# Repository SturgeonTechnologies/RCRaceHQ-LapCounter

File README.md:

# RCRaceHQ-LapCounter

Offline-first RC lap counter that runs on a Raspberry Pi 4 at the track and
syncs to [RC Race HQ](https://www.rcracehq.com). Decoding is done by
[OpenStint](https://github.com/zsellera/openstint) with an RTL-SDR; this repo
holds the services and web UI around it, and the hardware.

| Path | What |
|---|---|
| [`app/`](app) | The app: `lapd` (decoder feed → SQLite) + `web` (setup, admin, live view). Python, one container image |
| [`docs/design.md`](docs/design.md) | Architecture and build order |
| [`docs/club-sync.md`](docs/club-sync.md) | Club sync with RC Race HQ: pairing, event download, check-in, scoring, takeover |
| [`docs/linking.md`](docs/linking.md) | Linking a Pi to a club's track in RC Race HQ (Settings → Link) |
| [`docs/racing.md`](docs/racing.md) | Running a heat: start, countdown, laps, finish, results, qualifying |
| [`docs/event-sync.md`](docs/event-sync.md) | Downloading the club's events (Events page), the event pack format, transponders to learn |
| [`docs/build.md`](docs/build.md) | Building the image, CI → GHCR (native arm64), releases |
| [`hardware/burst-detector-hat/`](hardware/burst-detector-hat) | Burst-detector HAT for the Pi (KiCad, fab files) |
| [`hardware/lapcounter-hat/`](hardware/lapcounter-hat) | Rev 1.1 all-in-one HAT: baluns, track/pad relay, amp, detector, ID EEPROM |

## Where things live

- **This repo**: the code that runs as the service, and its image.
  CI tests every PR, builds `linux/arm64` on an arm64 runner, and on `main` /
  `v*` tags pushes to `ghcr.io/sturgeontechnologies/rcracehq-lapcounter`.
- **[RCRaceHQ-LapCounter-Deploy](https://github.com/SturgeonTechnologies/RCRaceHQ-LapCounter-Deploy)**:
  the Ansible. Provisions the Pi (OpenStint decoder, event hotspot + captive
  portal, SSM registration) and deploys a pinned image tag of this app with
  `deploy_lapcounter_app.yml`. It used to be `deploy/ansible/` here.

## Quick start

```bash
cd app
pip install -e '.[test]' && pytest       # tests
docker compose up --build                # web on :8080, lapd → 127.0.0.1:5556
```

Ship a version: merge to `main` (pushes `:sha-<7>`) or tag `vX.Y.Z` (pushes
`:vX.Y.Z`), then set `lapcounter_app_image_tag` in the deploy repo's inventory
and run its `deploy_lapcounter_app.yml`. Details in [docs/build.md](docs/build.md).

## License

Source-available. Software is [FSL-1.1-ALv2](LICENSE) (becomes Apache-2.0 two
years after each release); the HAT board in `hardware/` is
[CERN-OHL-S-2.0](hardware/LICENSE). Plain-language summary in
[LICENSING.md](LICENSING.md). "RC Race HQ" is a trademark of Sturgeon
Technologies LLC.

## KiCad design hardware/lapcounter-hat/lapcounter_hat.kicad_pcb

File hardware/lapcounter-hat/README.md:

# Lap counter HAT, rev 1.1 (all-in-one RF front end)

Raspberry Pi 4 HAT (65 × 56.5 mm, M2.5 HAT holes). Everything between the
loops and the RTL-SDR v3 is on this board: loop inputs, 1:9 baluns, the
track/pad relay, a 3–8 MHz band-pass, the LMH6624 amp with a bypass relay,
the burst detector and the HAT ID EEPROM.

```
track loop -> TB1 screw terminal -> T1 1:9 balun -+- or J1 SMA (balun + coax at the loop)
pad loop   -> TB2 screw terminal -> T2 1:9 balun -+- or J5 SMA
   -> K1 (GPIO22: off = TRACK, on = PAD; the other input is grounded)
   -> TVS -> 3–8 MHz band-pass -> K2 (GPIO27: off = AMP +21 dB, on = BYPASS)
   -> splitter -+-> J2 SMA -> RTL-SDR v3 (IDs via OpenStint)
                +-> AD8307 RSSI -> ADS1115 (I2C 0x48) + LM393 -> GPIO17 + BURST LED
U5 24C32 on ID_SD/ID_SC (pins 27/28), write-protected unless JP1 is bridged.
```

Use **either** the screw terminal **or** the SMA jack on each input, not both.
- Screw terminal: loop wire or twisted pair runs straight to the board; the on-board balun does the job.
- SMA jack: the club already has a balun at the loop and coax to the table.
Put a 390 Ω resistor across the far end of each loop either way.

## Ordering (JLCPCB)
- Gerbers: `fab/lapcounter_hat_gerbers.zip` (2 layers, 1.6 mm, HASL).
- Assembly (top side): `fab/bom_jlcpcb.csv` + `fab/cpl_jlcpcb.csv`.
  Check every LCSC part is in stock and the pin-1 rotation of U1–U5 in JLC's preview.
- Fit by hand: J3 2×20 stacking header, T1/T2 (hand-wound 1:9 on FT37-43,
  8 trifilar turns), optional J4 PoE pass-through.

## Bring-up
1. Power from the Pi. `i2cdetect -y 1` shows `48`.
2. Drive GPIO22 high (`pinctrl set 22 op dh`) -> PAD LED on, relay clicks. `dl` -> back to TRACK.
3. Drive GPIO27 high -> BYPASS LED on (amp out of the path).
4. Turn RV1 until BURST goes out with the loop empty, then back off a little.
5. Transponder on the loop: BURST LED on, OpenStint decodes through J2.
6. Bridge JP1, write the HAT EEPROM (serial + UUID), then clear JP1.

## Rebuild
`source ~/tools/kicad-env.sh && JAVA=... FREEROUTING=... tools/build.sh`
regenerates everything from `tools/design.py` (single source of truth),
autoroutes with Freerouting, runs ERC/DRC (`fab/reports/`) and rewrites `fab/`.

Licensed CERN-OHL-S-2.0 (see repository `LICENSING.md`).

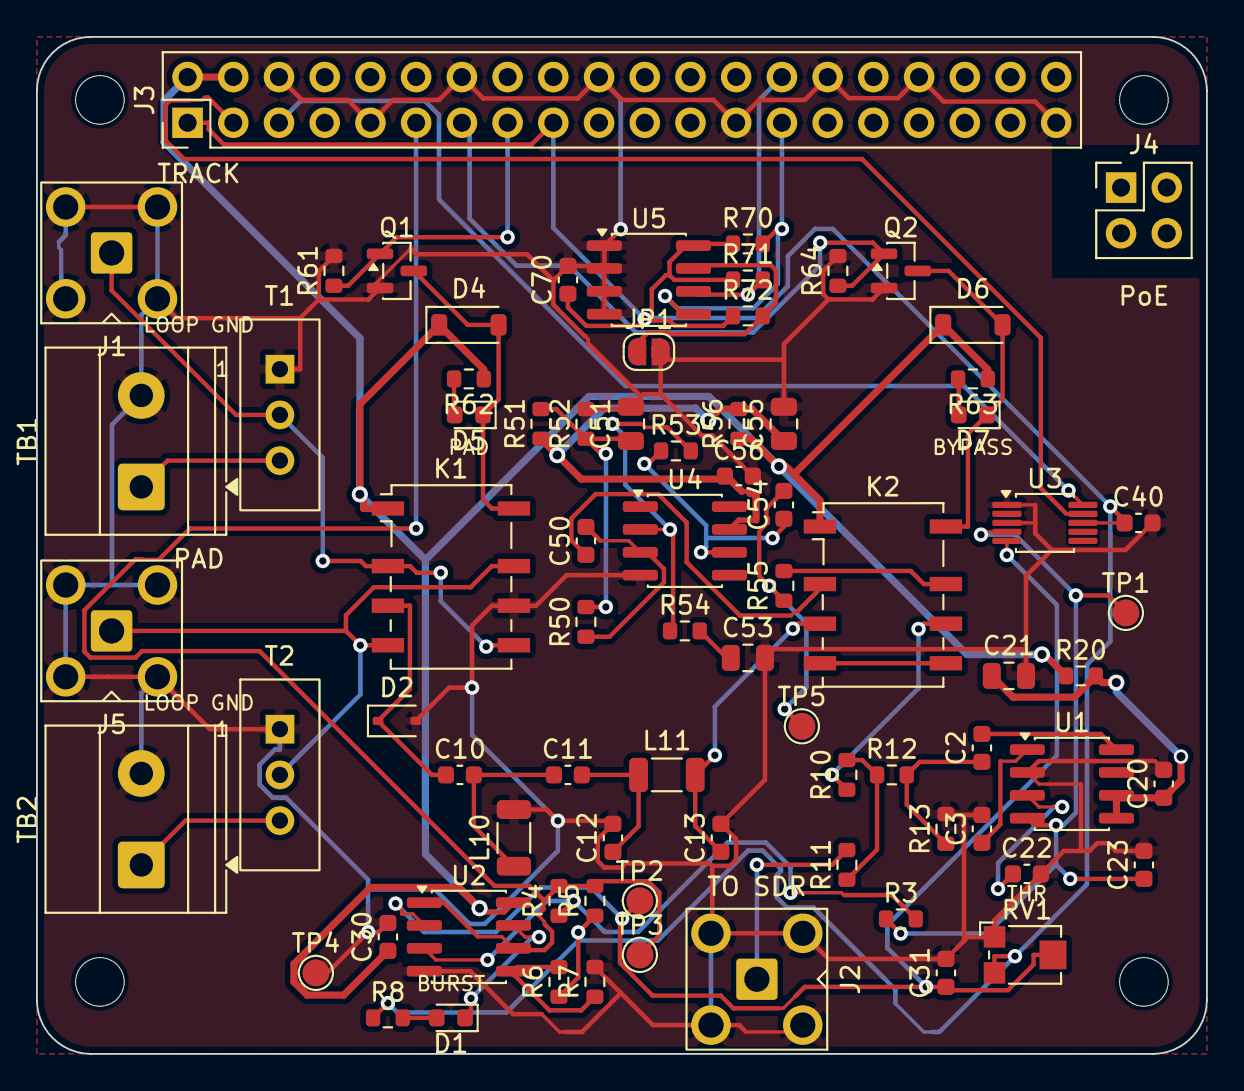
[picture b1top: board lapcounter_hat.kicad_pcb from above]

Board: 2 copper layers, 65.0 x 56.5 mm, 82 parts (0 on the bottom side), 47 nets.

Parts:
C2, C3: 10n; C_0603_1608Metric
C10, C11: 1n C0G; C_0603_1608Metric
C12, C13: 390p C0G; C_0603_1608Metric
C20, C30, C31, C40, C50, C54, C56, C70: 100n; C_0603_1608Metric
C21, C51, C53, C55: 10u; C_0805_2012Metric
C22: 1n; C_0603_1608Metric
C23: 470p C0G; C_0603_1608Metric
D1: BURST (green); LED_0603_1608Metric
D2: PESD5V0S1BA; D_SOD-323
D4, D6: 1N4148W; D_SOD-123
D5: PAD (green); LED_0603_1608Metric
D7: BYPASS (green); LED_0603_1608Metric
H1, H2, H3, H4: M2.5; MountingHole_2.7mm_M2.5
J1: TRACK (SMA); SMA_BAT_Wireless_BWSMA-KWE-Z001
J2: TO SDR; SMA_BAT_Wireless_BWSMA-KWE-Z001
J3: Pi GPIO (2x20 stacking); PinHeader_2x20_P2.54mm_Vertical
J4: PoE pass-through (not connected); PinHeader_2x02_P2.54mm_Vertical
J5: PAD (SMA); SMA_BAT_Wireless_BWSMA-KWE-Z001
JP1: WP (bridge to write); SolderJumper-2_P1.3mm_Open_RoundedPad1.0x1.5mm
K1: G6K-2F-Y 5V TRACK/PAD; Relay_DPDT_Omron_G6K-2F-Y
K2: G6K-2F-Y 5V AMP/BYPASS; Relay_DPDT_Omron_G6K-2F-Y
L10: 1.5u; L_1206_3216Metric
L11: 2.2u; L_1206_3216Metric
Q1, Q2: AO3400A; SOT-23
R3, R5, R6, R7, R51, R52, R72: 10k; R_0603_1608Metric
R4: 1M; R_0603_1608Metric
R8, R62, R63: 1k; R_0603_1608Metric
R10, R11, R12: 16.5; R_0603_1608Metric
R13: 52.3; R_0603_1608Metric
R20, R56: 10; R_0603_1608Metric
R50, R54, R55: 49.9; R_0603_1608Metric
R53: 1.05k; R_0603_1608Metric
R61, R64: 100k; R_0603_1608Metric
R70, R71: 3.9k; R_0603_1608Metric
RV1: 10k THRESHOLD; Potentiometer_Bourns_TC33X_Vertical
T1, T2: 1:9 FT37-43 (hand-wound); Toroid_FT37_Standing_3pad
TB1: TRACK LOOP; TerminalBlock_Phoenix_MKDS-1,5-2-5.08_1x02_P5.08mm_Horizont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
TB2: PAD LOOP; TerminalBlock_Phoenix_MKDS-1,5-2-5.08_1x02_P5.08mm_Horizont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
TP1: RSSI; TestPoint_Pad_D1.5mm
TP2: THRESH; TestPoint_Pad_D1.5mm
TP3: BURST; TestPoint_Pad_D1.5mm
TP4: GND; TestPoint_Pad_D1.5mm
TP5: AMP_OUT; TestPoint_Pad_D1.5mm
U1: AD8307ARZ; SOIC-8_3.9x4.9mm_P1.27mm
U2: LM393DR2G; SOIC-8_3.9x4.9mm_P1.27mm
U3: ADS1115IDGSR; MSOP-10_3x3mm_P0.5mm
U4: LMH6624MAX; SOIC-8_3.9x4.9mm_P1.27mm
U5: AT24C32; SOIC-8_3.9x4.9mm_P1.27mm

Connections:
+3V3: C40.1, C70.1, J3.1, J3.17, R5.1, R6.1, R8.1, R70.1, R71.1, R72.1, RV1.3, U3.8, U5.8
+5V: C30.1, D4.1, D6.1, J3.2, J3.4, K1.1, K2.1, R20.1, R56.1, R62.1, R63.1, U2.8
+5V_A: C20.1, C21.1, R20.2, U1.5, U1.6
+5V_AMP: C55.1, C56.1, R51.1, R56.2, U4.7
AMP_G: C53.1, R54.2
AMP_IN: C50.1, K2.2
AMP_N: R53.2, R54.1, U4.2
AMP_O: C54.1, R53.1, U4.6
AMP_OC: C54.2, R55.1, TP5.1
AMP_OUT: K2.7, R55.2
AMP_P: C50.2, R50.1, U4.3
BURST: J3.11, R4.2, R5.2, TP3.1, U2.1, U2.6
BYP: K2.4, K2.5
CMP_P: R3.2, R4.1, U2.3
EE_WP: JP1.1, R72.2, U5.7
GND: C3.2, C12.2, C13.2, C20.2, C21.2, C22.2, C23.2, C30.2, C31.2, C40.2, C51.2, C53.2, C55.2, C56.2, C70.2, D2.2, J1.2, J2.2, J3.6, J3.9, J3.14, J3.20, J3.25, J3.30, J3.34, J3.39, J5.2, JP1.2, K1.6, L10.2, Q1.2, Q2.2, R7.2, R13.2, R52.2, R61.2, R64.2, RV1.1, T1.1, T2.1, TB1.2, TB2.2, TP4.1, U1.2, U2.4, U3.1, U3.3, U4.4, U5.1, U5.2, U5.3, U5.4
HP1: C10.2, C11.1, L10.1
HP2: C11.2, C12.1, L11.1
ID_SC: J3.28, R71.2, U5.6
ID_SD: J3.27, R70.2, U5.5
INM: C3.1, U1.1
INP: C2.2, U1.8
K1_DRV: D4.2, D5.1, K1.8, Q1.3
K1_LED: D5.2, R62.2
K2_DRV: D6.2, D7.1, K2.8, Q2.3
K2_LED: D7.2, R63.2
LED_A: D1.2, R8.2
LED_K: D1.1, U2.7
OFS: C22.1, U1.3
PAD: J5.1, K1.4, K1.7, T2.2
PAD_HOT: T2.3, TB2.1
REF_B: R6.2, R7.1, U2.5
RF_A: C2.1, R12.2, R13.1
RF_FILT: C13.1, K2.3, L11.2
RF_SEL: C10.1, D2.1, K1.3
RSSI: C23.1, R3.1, TP1.1, U1.4, U3.4
SCL: J3.5, U3.10
SDA: J3.3, U3.9
SDR: J2.1, R11.2
SEL_BYP: J3.13, Q2.1, R64.1
SEL_PAD: J3.15, Q1.1, R61.1
SPLIT: R10.2, R11.1, R12.1
SPLIT_IN: K2.6, R10.1
THRESH: C31.1, RV1.2, TP2.1, U2.2, U3.5
TRK: J1.1, K1.2, K1.5, T1.2
TRK_HOT: T1.3, TB1.1
VBIAS: C51.1, R50.2, R51.2, R52.1

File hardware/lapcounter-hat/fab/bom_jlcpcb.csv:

Comment,Designator,Footprint,LCSC Part #
TRACK (SMA),J1,SMA_BAT_Wireless_BWSMA-KWE-Z001,C496551
TRACK LOOP,TB1,"TerminalBlock_Phoenix_MKDS-1,5-2-5.08_1x02_P5.08mm_Horizontal",C8465
PAD (SMA),J5,SMA_BAT_Wireless_BWSMA-KWE-Z001,C496551
PAD LOOP,TB2,"TerminalBlock_Phoenix_MKDS-1,5-2-5.08_1x02_P5.08mm_Horizontal",C8465
G6K-2F-Y 5V TRACK/PAD,K1,Relay_DPDT_Omron_G6K-2F-Y,C2982926
AO3400A,"Q1,Q2",SOT-23,C20917
100k,"R61,R64",R_0603_1608Metric,C25803
1N4148W,"D4,D6",D_SOD-123,C81598
PAD (green),D5,LED_0603_1608Metric,C12624
1k,"R62,R63,R8",R_0603_1608Metric,C21190
PESD5V0S1BA,D2,D_SOD-323,C19224
1n C0G,"C10,C11",C_0603_1608Metric,C1636
1.5u,L10,L_1206_3216Metric,C2885920
390p C0G,"C12,C13",C_0603_1608Metric,C1667
2.2u,L11,L_1206_3216Metric,C1048
G6K-2F-Y 5V AMP/BYPASS,K2,Relay_DPDT_Omron_G6K-2F-Y,C2982926
BYPASS (green),D7,LED_0603_1608Metric,C12624
LMH6624MAX,U4,SOIC-8_3.9x4.9mm_P1.27mm,C486023
100n,"C50,C54,C56,C20,C30,C31,C40,C70",C_0603_1608Metric,C14663
49.9,"R50,R54,R55",R_0603_1608Metric,C23185
10k,"R51,R52,R3,R5,R6,R7,R72",R_0603_1608Metric,C25804
10u,"C51,C53,C55,C21",C_0805_2012Metric,C15850
1.05k,R53,R_0603_1608Metric,C22832
10,"R56,R20",R_0603_1608Metric,C22859
TO SDR,J2,SMA_BAT_Wireless_BWSMA-KWE-Z001,C496551
16.5,"R10,R11,R12",R_0603_1608Metric,C12054
52.3,R13,R_0603_1608Metric,C81321
10n,"C2,C3",C_0603_1608Metric,C1589
AD8307ARZ,U1,SOIC-8_3.9x4.9mm_P1.27mm,C495272
1n,C22,C_0603_1608Metric,C1636
470p C0G,C23,C_0603_1608Metric,C36252
LM393DR2G,U2,SOIC-8_3.9x4.9mm_P1.27mm,C7955
1M,R4,R_0603_1608Metric,C22935
BURST (green),D1,LED_0603_1608Metric,C12624
10k THRESHOLD,RV1,Potentiometer_Bourns_TC33X_Vertical,C719176
ADS1115IDGSR,U3,MSOP-10_3x3mm_P0.5mm,C37593
AT24C32,U5,SOIC-8_3.9x4.9mm_P1.27mm,C2688466
3.9k,"R70,R71",R_0603_1608Metric,C23018

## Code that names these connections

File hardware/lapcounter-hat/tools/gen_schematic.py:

"""Generate lapcounter_hat.kicad_sch from design.py.

Every connected pin gets a short wire stub ending in a net label, so the
schematic reads as a net list rather than a wiring diagram. Unused pins get a
no-connect flag so ERC stays clean.
"""
import os
import pathlib
import re
import uuid

from design import NETS, NO_CONNECT, PARTS, PROJECT

HERE = pathlib.Path(__file__).resolve().parent.parent
SYMDIR = pathlib.Path(os.environ.get("KICAD9_SYMBOL_DIR", "/usr/share/kicad/symbols"))
ROOT = str(uuid.uuid5(uuid.NAMESPACE_URL, "sturgeon/lapcounter-hat-r11/root"))


def uid(*parts):
    # Stable UUIDs keep regenerated files diff-friendly.
    return str(uuid.uuid5(uuid.NAMESPACE_URL, "sturgeon/lapcounter-hat-r11/" + "/".join(parts)))


# ------------------------------------------------------- tiny s-expr parser --

TOKEN = re.compile(r'\(|\)|"(?:[^"\\]|\\.)*"|[^\s()]+')


def parse(text):
    stack, cur = [], []
    for m in TOKEN.finditer(text):
        t = m.group(0)
        if t == "(":
            stack.append(cur)
            cur = []
        elif t == ")":
            done, cur = cur, stack.pop()
            cur.append(done)
        else:
            cur.append(t)
    return cur[0]


def dump(node, indent=0):
    if not isinstance(node, list):
        return node
    pad = "  " * indent
    simple = all(not isinstance(c, list) for c in node)
    if simple:
        return "(" + " ".join(node) + ")"
    parts = [c for c in node if not isinstance(c, list)]
    kids = [c for c in node if isinstance(c, list)]
    s = "(" + " ".join(parts)
    for k in kids:
        s += "\n" + pad + "  " + dump(k, indent + 1)
    return s + ")"


def find(node, key):
    return [c for c in node if isinstance(c, list) and c and c[0] == key]


def unq(s):
    return s[1:-1] if s.startswith('"') else s


_libs = {}


def lib_symbol(lib_id):
    lib, name = lib_id.split(":")
    if lib not in _libs:
        path = HERE / f"{lib}.kicad_sym" if lib == PROJECT else SYMDIR / f"{lib}.kicad_sym"
        _libs[lib] = {unq(s[1]): s for s in find(parse(path.read_text()), "symbol")}
    sym = [list(x) if isinstance(x, list) else x for x in _libs[lib][name]]
    if find(sym, "extends"):
        raise SystemExit(f"{lib_id} uses extends; pick a base symbol")
    sym[1] = f'"{lib_id}"'
    return sym


def pins_of(sym):
    """{number: (x, y, angle)} in symbol coordinates (y up)."""
    out = {}

    def walk(n):
        for c in n:
            if isinstance(c, list):
                if c and c[0] == "pin":
                    at = find(c, "at")[0]
                    num = unq(find(c, "number")[0][1])
                    out[num] = (float(at[1]), float(at[2]), int(float(at[3])))
                else:
                    walk(c)
    walk(sym)
    return out


# ---------------------------------------------------------------- emitters --

def prop(name, value, x, y, hide=False, justify=None):
    h = " (hide yes)" if hide else ""
    j = f" (justify {justify})" if justify else ""
    return (f'    (property "{name}" "{value}" (at {x:.2f} {y:.2f} 0)\n'
            f'      (effects (font (size 1.27 1.27)){j}{h}))\n')


def symbol_instance(ref, part, pins):
    x, y = part["sch"]
    s = [f'  (symbol (lib_id "{part["sym"]}") (at {x:.2f} {y:.2f} 0) (unit 1)\n'
         f'    (exclude_from_sim no) (in_bom yes) (on_board yes) (dnp no)\n'
         f'    (uuid "{uid("sym", ref)}")\n']
    top = max([p[1] for p in pins.values()] + [2.54])
    s.append(prop("Reference", ref, x + 2.54, y - top - 3.81, justify="left"))
    s.append(prop("Value", part["value"], x + 2.54, y - top - 1.27, justify="left"))
    s.append(prop("Footprint", part["fp"], x, y, hide=True))
    s.append(prop("Datasheet", "", x, y, hide=True))
    if part.get("lcsc"):
        s.append(prop("LCSC", part["lcsc"], x, y, hide=True))
    for num in sorted(pins):
        s.append(f'    (pin "{num}" (uuid "{uid("pin", ref, num)}"))\n')
    s.append(f'    (instances (project "{PROJECT}" (path "/{ROOT}" '
             f'(reference "{ref}") (unit 1))))\n  )\n')
    return "".join(s)


def main():
    pad_net = {(r, p): n for n, members in NETS.items() for r, p in members}
    nc = set(NO_CONNECT)
    lib_syms, body = {}, []

    for ref, part in PARTS.items():
        sym = lib_symbol(part["sym"])
        lib_syms[part["sym"]] = sym
        pins = pins_of(sym)
        body.append(symbol_instance(ref, part, pins))
        sx, sy = part["sch"]
        for num, (px, py, ang) in pins.items():
            x, y = sx + px, sy - py               # schematic y points down
            if (ref, num) in nc:
                body.append(f'  (no_connect (at {x:.2f} {y:.2f}) (uuid "{uid("nc", ref, num)}"))\n')
                continue
            net = pad_net.get((ref, num))
            if net is None:
                raise SystemExit(f"{ref}.{num} is neither on a net nor marked no-connect")
            # Stub runs away from the body: opposite to the pin's direction.
            dx, dy = {0: (-1, 0), 90: (0, 1), 180: (1, 0), 270: (0, -1)}[ang]
            ex, ey = x + dx * 5.08, y + dy * 5.08
            body.append(f'  (wire (pts (xy {x:.2f} {y:.2f}) (xy {ex:.2f} {ey:.2f}))\n'
                        f'    (stroke (width 0) (type default)) (uuid "{uid("w", ref, num)}"))\n')
            angle, just = {(-1, 0): (180, "right"), (1, 0): (0, "left"),
                           (0, -1): (90, "left"), (0, 1): (270, "right")}[(dx, dy)]
            body.append(f'  (label "{net}" (at {ex:.2f} {ey:.2f} {angle})\n'
                        f'    (effects (font (size 1.27 1.27)) (justify {just}))\n'
                        f'    (uuid "{uid("lbl", ref, num)}"))\n')

    notes = [
        (20.32, 20.32, "Burst-detector HAT v0 (lap counter): loop -> splitter -> SDR + 3-8 MHz band-pass -> AD8307 RSSI -> LM393 -> GPIO17"),
        (20.32, 25.4, "J1 takes the loop's 1:9 balun coax. Resistive splitter (3x 16.5R) sends -6 dB to J2 (RTL-SDR) and -6 dB to the detector."),
        (20.32, 30.48, "Filter: 3 MHz T high-pass (1n/1.5u/1n) + 8 MHz pi low-pass (390p/2.2u/390p), 50 ohm; 52.3R terminates into the AD8307."),
        (20.32, 35.56, "RSSI = AD8307 OUT (25 mV/dB). RV1 sets THRESH (0-3.3 V). BURST is open-collector, pulled to 3.3 V: safe for Pi GPIO."),
        (20.32, 40.64, "ADS1115 at I2C 0x48 (ADDR=GND): AIN0 = RSSI, AIN1 = THRESH, ALERT/RDY -> GPIO27. J4 = PoE pins, pass-through only."),
    ]
    for i, (x, y, t) in enumerate(notes):
        body.append(f'  (text "{t}" (exclude_from_sim no) (at {x:.2f} {y:.2f} 0)\n'
                    f'    (effects (font (size 1.524 1.524)) (justify left))\n'
                    f'    (uuid "{uid("note", str(i))}"))\n')

    libs = "\n".join("    " + dump(s, 2) for s in lib_syms.values())
    out = (f'(kicad_sch (version 20250114) (generator "eeschema") (generator_version "9.0")\n'
           f'  (uuid "{ROOT}")\n  (paper "A4")\n'
           f'  (title_block (title "Lap counter burst-detector HAT") (rev "1.0") '
           f'(company "Sturgeon Technologies") (comment 1 "Generated by tools/gen_schematic.py"))\n'
           f'  (lib_symbols\n{libs}\n  )\n'
           + "".join(body) +
           '  (sheet_instances (path "/" (page "1")))\n  (embedded_fonts no)\n)\n')
    (HERE / f"{PROJECT}.kicad_sch").write_text(out)
    print("schematic written")


if __name__ == "__main__":
    main()

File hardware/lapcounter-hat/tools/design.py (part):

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Signal chain:
  track loop -> TB1 screw terminal -> T1 1:9 balun -+- J1 SMA (pre-made balun + coax)
  pad loop   -> TB2 screw terminal -> T2 1:9 balun -+- J5 SMA
      -> K1 (GPIO22: off = TRACK, on = PAD; the unselected input is shorted to GND)
      -> TVS -> 3 MHz high-pass -> 8 MHz low-pass (50 ohm)
      -> K2 (GPIO27: off = AMP, on = BYPASS) -> LMH6624, +21 dB into 50 ohm
      -> resistive splitter -+-> J2 SMA -> RTL-SDR v3 (IDs, via OpenStint)
                             +-> AD8307 log detector -> RSSI -+-> ADS1115 AIN0 (I2C 0x48)
                                                              +-> LM393 vs RV1 -> GPIO17 + LED
  U5 24C32 on ID_SD/ID_SC (pins 27/28) = Pi HAT ID EEPROM, write-protected
  unless JP1 is bridged.
"""

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

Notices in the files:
hardware/lapcounter-hat/lapcounter_hat.kicad_pcb:
(c) 2026 Sturgeon Technologies LLC - CERN-OHL-S-2.0
hardware/lapcounter-hat/tools/design.py:
Back silkscreen (mirrored), centred: CERN-OHL-S source location + serial box.
